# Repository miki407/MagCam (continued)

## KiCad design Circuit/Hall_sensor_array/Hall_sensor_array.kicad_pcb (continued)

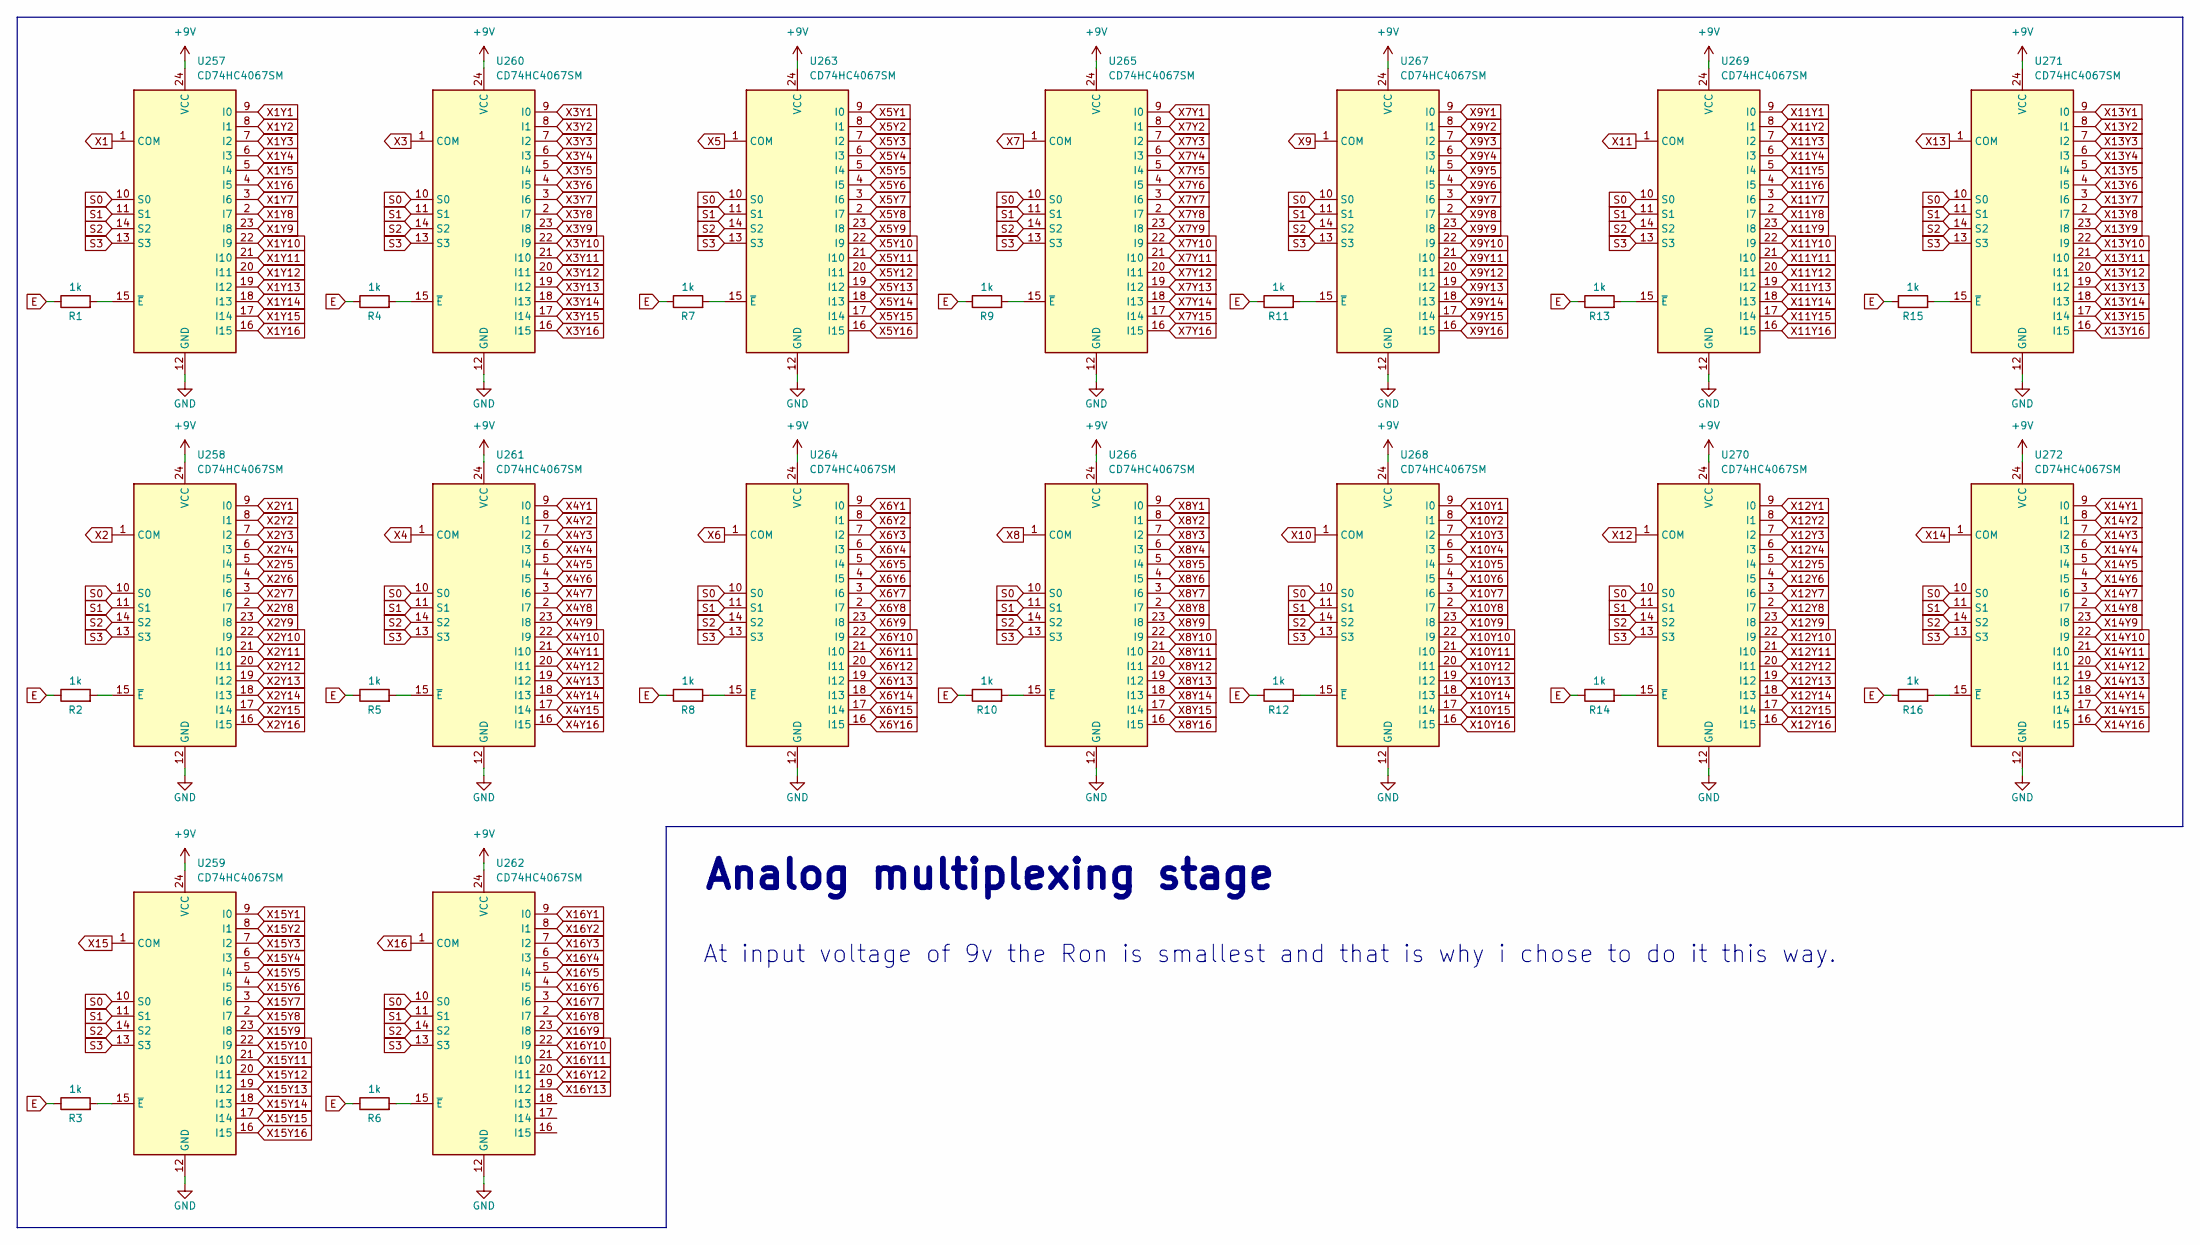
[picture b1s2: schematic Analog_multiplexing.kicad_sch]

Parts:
R1, R2, R3, R4, R5, R6, R7, R8, R9, R10, R11, R12, R13, R14, R15, R16: 1k
U257, U258, U259, U260, U261, U262, U263, U264, U265, U266, U267, U268, U269, U270, U271, U272: CD74HC4067SM; TSSOP-24_4.4x7.8mm_P0.65mm

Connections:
+9V: U257.24 (VCC), U258.24 (VCC), U259.24 (VCC), U260.24 (VCC), U261.24 (VCC), U262.24 (VCC), U263.24 (VCC), U264.24 (VCC), U265.24 (VCC), U266.24 (VCC), U267.24 (VCC), U268.24 (VCC), U269.24 (VCC), U270.24 (VCC), U271.24 (VCC), U272.24 (VCC)
GND: U257.12 (GND), U258.12 (GND), U259.12 (GND), U260.12 (GND), U261.12 (GND), U262.12 (GND), U263.12 (GND), U264.12 (GND), U265.12 (GND), U266.12 (GND), U267.12 (GND), U268.12 (GND), U269.12 (GND), U270.12 (GND), U271.12 (GND), U272.12 (GND); also elsewhere on the board
unnamed: R1.1, R2.1, R3.1, R4.1, R5.1, R6.1, R7.1, R8.1, R9.1, R10.1, R11.1, R12.1, R13.1, R14.1, R15.1, R16.1
unnamed: R1.2, U257.15 (~E)
unnamed: R2.2, U258.15 (~E)
unnamed: R3.2, U259.15 (~E)
unnamed: R4.2, U260.15 (~E)
unnamed: R5.2, U261.15 (~E)
unnamed: R6.2, U262.15 (~E)
unnamed: R7.2, U263.15 (~E)
unnamed: R8.2, U264.15 (~E)
unnamed: R9.2, U265.15 (~E)
unnamed: R10.2, U266.15 (~E)
unnamed: R11.2, U267.15 (~E)
unnamed: R12.2, U268.15 (~E)
unnamed: R13.2, U269.15 (~E)
unnamed: R14.2, U270.15 (~E)
unnamed: R15.2, U271.15 (~E)
unnamed: R16.2, U272.15 (~E)
S0: U257.10 (S0), U258.10 (S0), U259.10 (S0), U260.10 (S0), U261.10 (S0), U262.10 (S0), U263.10 (S0), U264.10 (S0), U265.10 (S0), U266.10 (S0), U267.10 (S0), U268.10 (S0), U269.10 (S0), U270.10 (S0), U271.10 (S0), U272.10 (S0)
S1: U257.11 (S1), U258.11 (S1), U259.11 (S1), U260.11 (S1), U261.11 (S1), U262.11 (S1), U263.11 (S1), U264.11 (S1), U265.11 (S1), U266.11 (S1), U267.11 (S1), U268.11 (S1), U269.11 (S1), U270.11 (S1), U271.11 (S1), U272.11 (S1)
S2: U257.14 (S2), U258.14 (S2), U259.14 (S2), U260.14 (S2), U261.14 (S2), U262.14 (S2), U263.14 (S2), U264.14 (S2), U265.14 (S2), U266.14 (S2), U267.14 (S2), U268.14 (S2), U269.14 (S2), U270.14 (S2), U271.14 (S2), U272.14 (S2)
S3: U257.13 (S3), U258.13 (S3), U259.13 (S3), U260.13 (S3), U261.13 (S3), U262.13 (S3), U263.13 (S3), U264.13 (S3), U265.13 (S3), U266.13 (S3), U267.13 (S3), U268.13 (S3), U269.13 (S3), U270.13 (S3), U271.13 (S3), U272.13 (S3)
X1: U257.1 (COM)
X1Y1: U257.9 (I0); also elsewhere on the board
X1Y2: U257.8 (I1); also elsewhere on the board
X1Y3: U257.7 (I2); also elsewhere on the board
X1Y4: U257.6 (I3); also elsewhere on the board
X1Y5: U257.5 (I4); also elsewhere on the board
X1Y6: U257.4 (I5); also elsewhere on the board
X1Y7: U257.3 (I6); also elsewhere on the board
X1Y8: U257.2 (I7); also elsewhere on the board
X1Y9: U257.23 (I8); also elsewhere on the board
X1Y10: U257.22 (I9); also elsewhere on the board
X1Y11: U257.21 (I10); also elsewhere on the board
X1Y12: U257.20 (I11); also elsewhere on the board
X1Y13: U257.19 (I12); also elsewhere on the board
X1Y14: U257.18 (I13); also elsewhere on the board
X1Y15: U257.17 (I14); also elsewhere on the board
X1Y16: U257.16 (I15); also elsewhere on the board
X2: U258.1 (COM)
X2Y1: U258.9 (I0); also elsewhere on the board
X2Y2: U258.8 (I1); also elsewhere on the board
X2Y3: U258.7 (I2); also elsewhere on the board
X2Y4: U258.6 (I3); also elsewhere on the board
X2Y5: U258.5 (I4); also elsewhere on the board
X2Y6: U258.4 (I5); also elsewhere on the board
X2Y7: U258.3 (I6); also elsewhere on the board
X2Y8: U258.2 (I7); also elsewhere on the board
X2Y9: U258.23 (I8); also elsewhere on the board
X2Y10: U258.22 (I9); also elsewhere on the board
X2Y11: U258.21 (I10); also elsewhere on the board
X2Y12: U258.20 (I11); also elsewhere on the board
X2Y13: U258.19 (I12); also elsewhere on the board
X2Y14: U258.18 (I13); also elsewhere on the board
X2Y15: U258.17 (I14); also elsewhere on the board
X2Y16: U258.16 (I15); also elsewhere on the board
X3: U260.1 (COM)
X3Y1: U260.9 (I0); also elsewhere on the board
X3Y2: U260.8 (I1); also elsewhere on the board
X3Y3: U260.7 (I2); also elsewhere on the board
X3Y4: U260.6 (I3); also elsewhere on the board
X3Y5: U260.5 (I4); also elsewhere on the board
X3Y6: U260.4 (I5); also elsewhere on the board
X3Y7: U260.3 (I6); also elsewhere on the board
X3Y8: U260.2 (I7); also elsewhere on the board
X3Y9: U260.23 (I8); also elsewhere on the board
X3Y10: U260.22 (I9); also elsewhere on the board
X3Y11: U260.21 (I10); also elsewhere on the board
X3Y12: U260.20 (I11); also elsewhere on the board
X3Y13: U260.19 (I12); also elsewhere on the board
X3Y14: U260.18 (I13); also elsewhere on the board
X3Y15: U260.17 (I14); also elsewhere on the board
X3Y16: U260.16 (I15); also elsewhere on the board
X4: U261.1 (COM)
X4Y1: U261.9 (I0); also elsewhere on the board
X4Y2: U261.8 (I1); also elsewhere on the board
X4Y3: U261.7 (I2); also elsewhere on the board
X4Y4: U261.6 (I3); also elsewhere on the board
X4Y5: U261.5 (I4); also elsewhere on the board
X4Y6: U261.4 (I5); also elsewhere on the board
X4Y7: U261.3 (I6); also elsewhere on the board
X4Y8: U261.2 (I7); also elsewhere on the board
X4Y9: U261.23 (I8); also elsewhere on the board
X4Y10: U261.22 (I9); also elsewhere on the board
X4Y11: U261.21 (I10); also elsewhere on the board
X4Y12: U261.20 (I11); also elsewhere on the board
X4Y13: U261.19 (I12); also elsewhere on the board
X4Y14: U261.18 (I13); also elsewhere on the board
X4Y15: U261.17 (I14); also elsewhere on the board
X4Y16: U261.16 (I15); also elsewhere on the board
X5: U263.1 (COM)
X5Y1: U263.9 (I0); also elsewhere on the board
X5Y2: U263.8 (I1); also elsewhere on the board
X5Y3: U263.7 (I2); also elsewhere on the board
X5Y4: U263.6 (I3); also elsewhere on the board
X5Y5: U263.5 (I4); also elsewhere on the board
X5Y6: U263.4 (I5); also elsewhere on the board
X5Y7: U263.3 (I6); also elsewhere on the board
X5Y8: U263.2 (I7); also elsewhere on the board
X5Y9: U263.23 (I8); also elsewhere on the board
X5Y10: U263.22 (I9); also elsewhere on the board
X5Y11: U263.21 (I10); also elsewhere on the board
X5Y12: U263.20 (I11); also elsewhere on the board
X5Y13: U263.19 (I12); also elsewhere on the board
X5Y14: U263.18 (I13); also elsewhere on the board
X5Y15: U263.17 (I14); also elsewhere on the board
X5Y16: U263.16 (I15); also elsewhere on the board
X6: U264.1 (COM)
X6Y1: U264.9 (I0); also elsewhere on the board
X6Y2: U264.8 (I1); also elsewhere on the board
X6Y3: U264.7 (I2); also elsewhere on the board
X6Y4: U264.6 (I3); also elsewhere on the board
X6Y5: U264.5 (I4); also elsewhere on the board
X6Y6: U264.4 (I5); also elsewhere on the board
X6Y7: U264.3 (I6); also elsewhere on the board
X6Y8: U264.2 (I7); also elsewhere on the board
X6Y9: U264.23 (I8); also elsewhere on the board
X6Y10: U264.22 (I9); also elsewhere on the board
X6Y11: U264.21 (I10); also elsewhere on the board
X6Y12: U264.20 (I11); also elsewhere on the board
X6Y13: U264.19 (I12); also elsewhere on the board
X6Y14: U264.18 (I13); also elsewhere on the board
X6Y15: U264.17 (I14); also elsewhere on the board
X6Y16: U264.16 (I15); also elsewhere on the board
X7: U265.1 (COM)
X7Y1: U265.9 (I0); also elsewhere on the board
X7Y2: U265.8 (I1); also elsewhere on the board
X7Y3: U265.7 (I2); also elsewhere on the board
X7Y4: U265.6 (I3); also elsewhere on the board
X7Y5: U265.5 (I4); also elsewhere on the board
X7Y6: U265.4 (I5); also elsewhere on the board
X7Y7: U265.3 (I6); also elsewhere on the board
X7Y8: U265.2 (I7); also elsewhere on the board
X7Y9: U265.23 (I8); also elsewhere on the board
X7Y10: U265.22 (I9); also elsewhere on the board
X7Y11: U265.21 (I10); also elsewhere on the board
X7Y12: U265.20 (I11); also elsewhere on the board
X7Y13: U265.19 (I12); also elsewhere on the board
X7Y14: U265.18 (I13); also elsewhere on the board
X7Y15: U265.17 (I14); also elsewhere on the board
X7Y16: U265.16 (I15); also elsewhere on the board
X8: U266.1 (COM)
X8Y1: U266.9 (I0); also elsewhere on the board
X8Y2: U266.8 (I1); also elsewhere on the board
X8Y3: U266.7 (I2); also elsewhere on the board
X8Y4: U266.6 (I3); also elsewhere on the board
X8Y5: U266.5 (I4); also elsewhere on the board
X8Y6: U266.4 (I5); also elsewhere on the board
X8Y7: U266.3 (I6); also elsewhere on the board
X8Y8: U266.2 (I7); also elsewhere on the board
X8Y9: U266.23 (I8); also elsewhere on the board
X8Y10: U266.22 (I9); also elsewhere on the board
X8Y11: U266.21 (I10); also elsewhere on the board
X8Y12: U266.20 (I11); also elsewhere on the board
X8Y13: U266.19 (I12); also elsewhere on the board
X8Y14: U266.18 (I13); also elsewhere on the board
X8Y15: U266.17 (I14); also elsewhere on the board
X8Y16: U266.16 (I15); also elsewhere on the board
X9: U267.1 (COM)
X9Y1: U267.9 (I0); also elsewhere on the board
X9Y2: U267.8 (I1); also elsewhere on the board
X9Y3: U267.7 (I2); also elsewhere on the board
X9Y4: U267.6 (I3); also elsewhere on the board
X9Y5: U267.5 (I4); also elsewhere on the board
X9Y6: U267.4 (I5); also elsewhere on the board
X9Y7: U267.3 (I6); also elsewhere on the board
X9Y8: U267.2 (I7); also elsewhere on the board
X9Y9: U267.23 (I8); also elsewhere on the board
X9Y10: U267.22 (I9); also elsewhere on the board
X9Y11: U267.21 (I10); also elsewhere on the board
X9Y12: U267.20 (I11); also elsewhere on the board
X9Y13: U267.19 (I12); also elsewhere on the board
X9Y14: U267.18 (I13); also elsewhere on the board
X9Y15: U267.17 (I14); also elsewhere on the board
X9Y16: U267.16 (I15); also elsewhere on the board
X10: U268.1 (COM)
X10Y1: U268.9 (I0); also elsewhere on the board
X10Y2: U268.8 (I1); also elsewhere on the board
X10Y3: U268.7 (I2); also elsewhere on the board
X10Y4: U268.6 (I3); also elsewhere on the board
X10Y5: U268.5 (I4); also elsewhere on the board
X10Y6: U268.4 (I5); also elsewhere on the board
X10Y7: U268.3 (I6); also elsewhere on the board
X10Y8: U268.2 (I7); also elsewhere on the board
X10Y9: U268.23 (I8); also elsewhere on the board
X10Y10: U268.22 (I9); also elsewhere on the board
X10Y11: U268.21 (I10); also elsewhere on the board
X10Y12: U268.20 (I11); also elsewhere on the board
X10Y13: U268.19 (I12); also elsewhere on the board
X10Y14: U268.18 (I13); also elsewhere on the board
X10Y15: U268.17 (I14); also elsewhere on the board
X10Y16: U268.16 (I15); also elsewhere on the board
X11: U269.1 (COM)
X11Y1: U269.9 (I0); also elsewhere on the board
X11Y2: U269.8 (I1); also elsewhere on the board
X11Y3: U269.7 (I2); also elsewhere on the board
X11Y4: U269.6 (I3); also elsewhere on the board
X11Y5: U269.5 (I4); also elsewhere on the board
X11Y6: U269.4 (I5); also elsewhere on the board
X11Y7: U269.3 (I6); also elsewhere on the board
X11Y8: U269.2 (I7); also elsewhere on the board
X11Y9: U269.23 (I8); also elsewhere on the board
X11Y10: U269.22 (I9); also elsewhere on the board
X11Y11: U269.21 (I10); also elsewhere on the board
X11Y12: U269.20 (I11); also elsewhere on the board
X11Y13: U269.19 (I12); also elsewhere on the board
X11Y14: U269.18 (I13); also elsewhere on the board
X11Y15: U269.17 (I14); also elsewhere on the board
X11Y16: U269.16 (I15); also elsewhere on the board
X12: U270.1 (COM)
X12Y1: U270.9 (I0); also elsewhere on the board
X12Y2: U270.8 (I1); also elsewhere on the board
X12Y3: U270.7 (I2); also elsewhere on the board
X12Y4: U270.6 (I3); also elsewhere on the board
X12Y5: U270.5 (I4); also elsewhere on the board
X12Y6: U270.4 (I5); also elsewhere on the board
X12Y7: U270.3 (I6); also elsewhere on the board
X12Y8: U270.2 (I7); also elsewhere on the board
X12Y9: U270.23 (I8); also elsewhere on the board
X12Y10: U270.22 (I9); also elsewhere on the board
X12Y11: U270.21 (I10); also elsewhere on the board
X12Y12: U270.20 (I11); also elsewhere on the board
X12Y13: U270.19 (I12); also elsewhere on the board
X12Y14: U270.18 (I13); also elsewhere on the board
X12Y15: U270.17 (I14); also elsewhere on the board
X12Y16: U270.16 (I15); also elsewhere on the board
X13: U271.1 (COM)
X13Y1: U271.9 (I0); also elsewhere on the board
X13Y2: U271.8 (I1); also elsewhere on the board
X13Y3: U271.7 (I2); also elsewhere on the board
X13Y4: U271.6 (I3); also elsewhere on the board
X13Y5: U271.5 (I4); also elsewhere on the board
X13Y6: U271.4 (I5); also elsewhere on the board
X13Y7: U271.3 (I6); also elsewhere on the board
X13Y8: U271.2 (I7); also elsewhere on the board
X13Y9: U271.23 (I8); also elsewhere on the board
X13Y10: U271.22 (I9); also elsewhere on the board
X13Y11: U271.21 (I10); also elsewhere on the board
X13Y12: U271.20 (I11); also elsewhere on the board
X13Y13: U271.19 (I12); also elsewhere on the board
X13Y14: U271.18 (I13); also elsewhere on the board
X13Y15: U271.17 (I14); also elsewhere on the board
X13Y16: U271.16 (I15); also elsewhere on the board
X14: U272.1 (COM)
X14Y1: U272.9 (I0); also elsewhere on the board
X14Y2: U272.8 (I1); also elsewhere on the board
X14Y3: U272.7 (I2); also elsewhere on the board
X14Y4: U272.6 (I3); also elsewhere on the board
X14Y5: U272.5 (I4); also elsewhere on the board
X14Y6: U272.4 (I5); also elsewhere on the board
X14Y7: U272.3 (I6); also elsewhere on the board
X14Y8: U272.2 (I7); also elsewhere on the board
X14Y9: U272.23 (I8); also elsewhere on the board
X14Y10: U272.22 (I9); also elsewhere on the board
X14Y11: U272.21 (I10); also elsewhere on the board
X14Y12: U272.20 (I11); also elsewhere on the board
X14Y13: U272.19 (I12); also elsewhere on the board
X14Y14: U272.18 (I13); also elsewhere on the board
X14Y15: U272.17 (I14); also elsewhere on the board
X14Y16: U272.16 (I15); also elsewhere on the board
X15: U259.1 (COM)
X15Y1: U259.9 (I0); also elsewhere on the board
X15Y2: U259.8 (I1); also elsewhere on the board
X15Y3: U259.7 (I2); also elsewhere on the board
X15Y4: U259.6 (I3); also elsewhere on the board
X15Y5: U259.5 (I4); also elsewhere on the board
X15Y6: U259.4 (I5); also elsewhere on the board
X15Y7: U259.3 (I6); also elsewhere on the board
X15Y8: U259.2 (I7); also elsewhere on the board
X15Y9: U259.23 (I8); also elsewhere on the board
X15Y10: U259.22 (I9); also elsewhere on the board
X15Y11: U259.21 (I10); also elsewhere on the board
X15Y12: U259.20 (I11); also elsewhere on the board
X15Y13: U259.19 (I12); also elsewhere on the board
X15Y14: U259.18 (I13); also elsewhere on the board
X15Y15: U259.17 (I14); also elsewhere on the board
X15Y16: U259.16 (I15); also elsewhere on the board
X16: U262.1 (COM)
X16Y1: U262.9 (I0); also elsewhere on the board
X16Y2: U262.8 (I1); also elsewhere on the board
X16Y3: U262.7 (I2); also elsewhere on the board
X16Y4: U262.6 (I3); also elsewhere on the board
X16Y5: U262.5 (I4); also elsewhere on the board
X16Y6: U262.4 (I5); also elsewhere on the board
X16Y7: U262.3 (I6); also elsewhere on the board
X16Y8: U262.2 (I7); also elsewhere on the board
X16Y9: U262.23 (I8); also elsewhere on the board
X16Y10: U262.22 (I9); also elsewhere on the board
X16Y11: U262.21 (I10); also elsewhere on the board
X16Y12: U262.20 (I11); also elsewhere on the board
X16Y13: U262.19 (I12); also elsewhere on the board

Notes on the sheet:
At input voltage of 9v the Ron is smallest and that is why i chose to do it this way.
Analog multiplexing stage

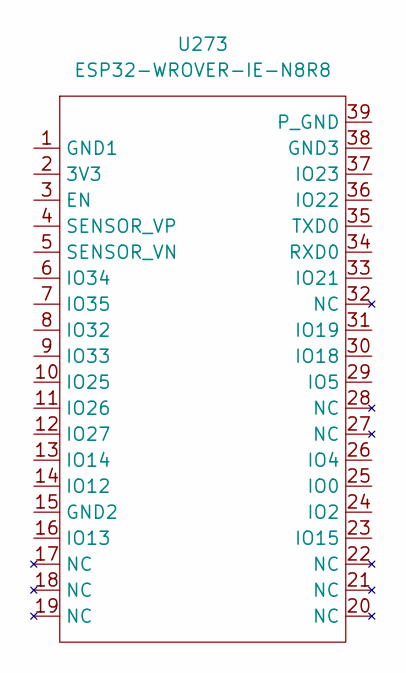
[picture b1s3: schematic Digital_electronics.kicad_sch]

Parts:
U273: ESP32-WROVER-IE-N8R8

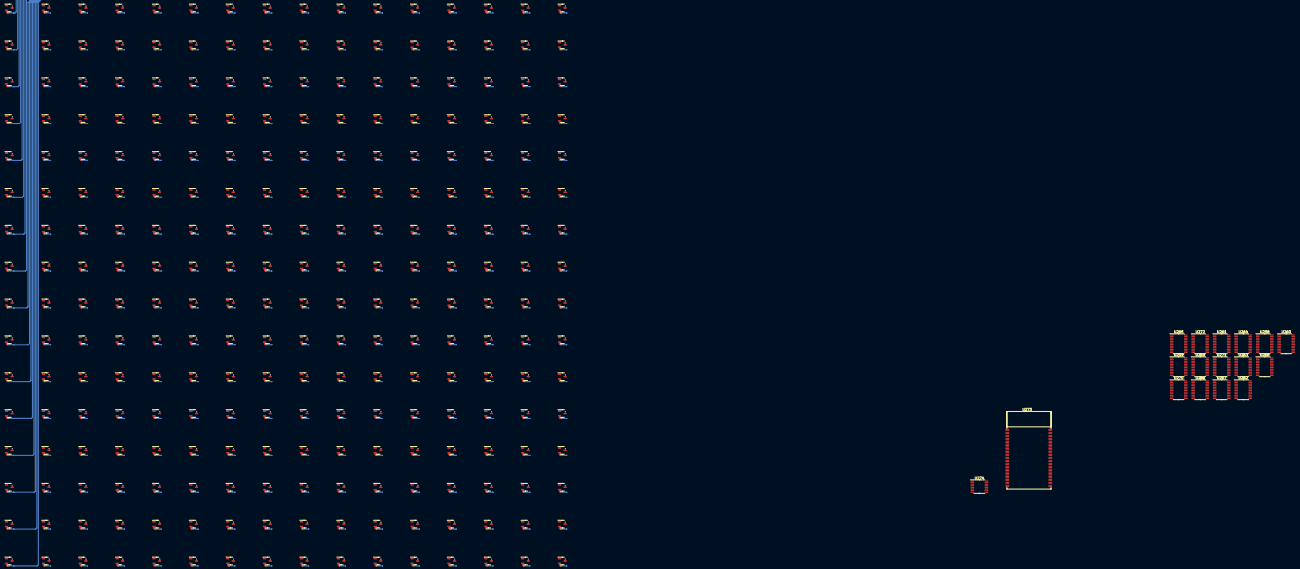
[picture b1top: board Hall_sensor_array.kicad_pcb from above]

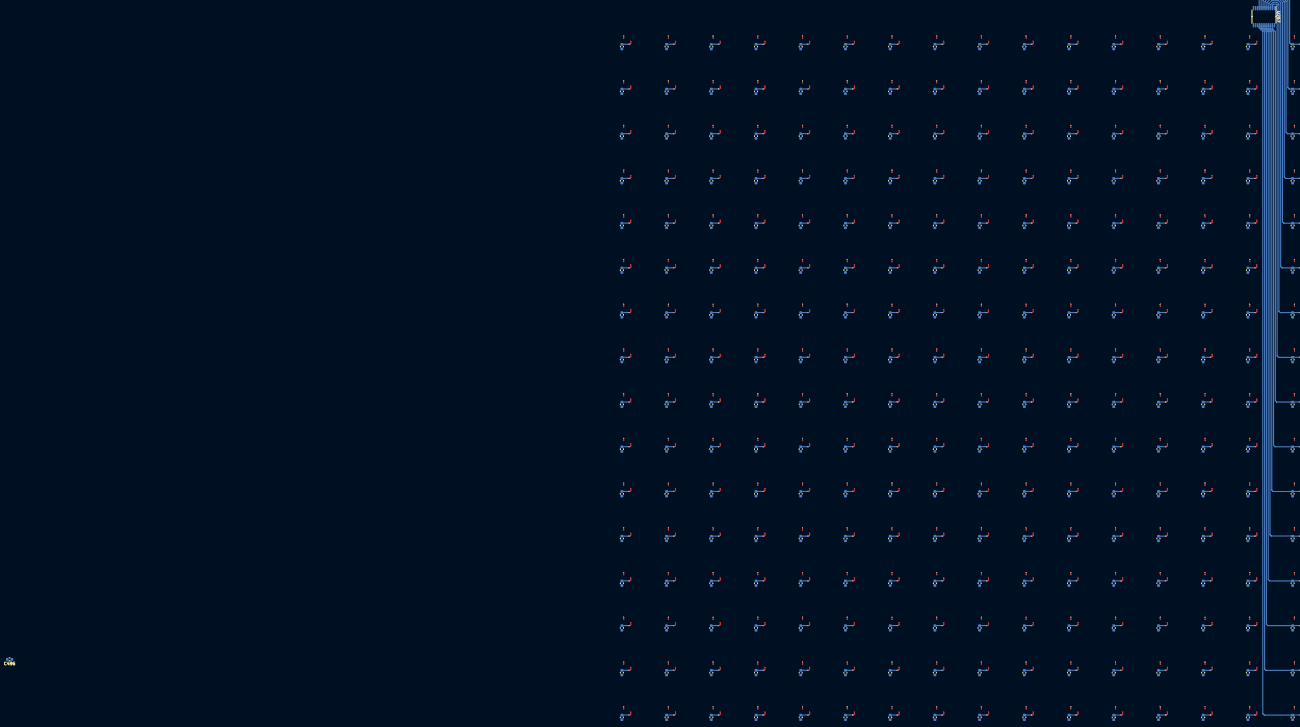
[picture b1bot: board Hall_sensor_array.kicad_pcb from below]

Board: 2 copper layers, 531 parts (258 on the bottom side), 263 nets.

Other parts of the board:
C496: 10n; C_0603_1608Metric
U274: ADS7830; TSSOP-16_4.4x5mm_P0.65mm

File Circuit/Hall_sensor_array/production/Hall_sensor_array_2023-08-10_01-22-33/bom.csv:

Designator,Footprint,Quantity,Value,LCSC Part #
"C1, C10, C100, C101, C102, C103, C104, C105, C106, C107, C108, C109, C11, C110, C111, C112, C113, C114, C115, C116, C117, C118, C119, C12, C120, C121, C122, C123, C124, C125, C126, C127, C128, C129, C13, C130, C131, C132, C133, C134, C135, C136, C137, C138, C139, C14, C140, C141, C142, C143, C144, C145, C146, C147, C148, C149, C15, C150, C151, C152, C153, C154, C155, C156, C157, C158, C159, C16, C160, C161, C162, C163, C164, C165, C166, C167, C168, C169, C17, C170, C171, C172, C173, C174, C175, C176, C177, C178, C179, C18, C180, C181, C182, C183, C184, C185, C186, C187, C188, C189, C19, C190, C191, C192, C193, C194, C195, C196, C197, C198, C199, C2, C20, C200, C201, C202, C203, C204, C205, C206, C207, C208, C209, C21, C210, C211, C212, C213, C214, C215, C216, C217, C218, C219, C22, C220, C221, C222, C223, C224, C225, C226, C227, C228, C229, C23, C230, C231, C232, C233, C234, C235, C236, C237, C238, C239, C24, C240, C241, C242, C243, C244, C245, C246, C247, C248, C249, C25, C250, C251, C252, C253, C254, C255, C256, C26, C27, C28, C29, C3, C30, C31, C32, C33, C34, C35, C36, C37, C38, C39, C4, C40, C41, C42, C43, C44, C45, C46, C47, C48, C49, C5, C50, C51, C52, C53, C54, C55, C56, C57, C58, C59, C6, C60, C61, C62, C63, C64, C65, C66, C67, C68, C69, C7, C70, C71, C72, C73, C74, C75, C76, C77, C78, C79, C8, C80, C81, C82, C83, C84, C85, C86, C87, C88, C89, C9, C90, C91, C92, C93, C94, C95, C96, C97, C98, C99",0603,256,100p,
"C257, C258, C259, C260, C261, C262",0805,6,22u,
"C301, C302, C303, C304, C305, C306, C307, C308, C309, C310, C311, C312, C313, C314, C315, C316, C317",0603,17,100n,
"D1, D2, D3, D4, D5, D6, D7",0805,7,LED,
J501,PinHeader_1x05_P2.54mm_Horizontal,1,Conn_01x05_Socket,
"R18, R19, R20, R21, R22, R23, R24",0805,7,470,
R25,0805,1,10k,
"U1, U10, U100, U101, U102, U103, U104, U105, U106, U107, U108, U109, U11, U110, U111, U112, U113, U114, U115, U116, U117, U118, U119, U12, U120, U121, U122, U123, U124, U125, U126, U127, U128, U129, U13, U130, U131, U132, U133, U134, U135, U136, U137, U138, U139, U14, U140, U141, U142, U143, U144, U145, U146, U147, U148, U149, U15, U150, U151, U152, U153, U154, U155, U156, U157, U158, U159, U16, U160, U161, U162, U163, U164, U165, U166, U167, U168, U169, U17, U170, U171, U172, U173, U174, U175, U176, U177, U178, U179, U18, U180, U181, U182, U183, U184, U185, U186, U187, U188, U189, U19, U190, U191, U192, U193, U194, U195, U196, U197, U198, U199, U2, U20, U200, U201, U202, U203, U204, U205, U206, U207, U208, U209, U21, U210, U211, U212, U213, U214, U215, U216, U217, U218, U219, U22, U220, U221, U222, U223, U224, U225, U226, U227, U228, U229, U23, U230, U231, U232, U233, U234, U235, U236, U237, U238, U239, U24, U240, U241, U242, U243, U244, U245, U246, U247, U248, U249, U25, U250, U251, U252, U253, U254, U255, U256, U26, U27, U28, U29, U3, U30, U31, U32, U33, U34, U35, U36, U37, U38, U39, U4, U40, U41, U42, U43, U44, U45, U46, U47, U48, U49, U5, U50, U51, U52, U53, U54, U55, U56, U57, U58, U59, U6, U60, U61, U62, U63, U64, U65, U66, U67, U68, U69, U7, U70, U71, U72, U73, U74, U75, U76, U77, U78, U79, U8, U80, U81, U82, U83, U84, U85, U86, U87, U88, U89, U9, U90, U91, U92, U93, U94, U95, U96, U97, U98, U99",SOT-23-3,256,AH49HSC,
"U257, U258, U259, U260, U261, U262, U263, U264, U265, U266, U267, U268, U269, U270, U271, U272, U276",TSSOP-24_4.4x7.8mm_P0.65mm,17,CD74HC4067SM,
U273,TO-252-2,1,ZD1117ILTR50,
U274,TO-252-2,1,78D06LL-TN3-R,
U275,TO-252-2,1,AZ1117D-3.3,
U277,SOIC-16_3.9x9.9mm_P1.27mm,1,4040,

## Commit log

2022-12-23 Added Circuit(unfinished)
    I just strated learing how to use KiCAD. This circuit will take some time to finish.
    The PCB files are also inside
2022-12-24 Updated circuit(work in progress)
2022-12-31 Updated circuit
    Added binary counter for selecting analog multiplexer address
2023-01-23 Big progress on the project
2023-02-02 Updated PCB/Fixed Curcuit
2023-02-05 Added autonomous
2023-02-21 latest update
2023-08-09 Major update! New pcb
    i did some work
2023-09-01 V0.1a
    First release of the version 0.1 of this project.
2023-09-01 V0.1b
    - Updated README
    - Fixed
    > Bug where pause feature didn't work as intended
    > Bug where reset was inverted in Firmware V0.2
2023-09-01 Create CNAME
